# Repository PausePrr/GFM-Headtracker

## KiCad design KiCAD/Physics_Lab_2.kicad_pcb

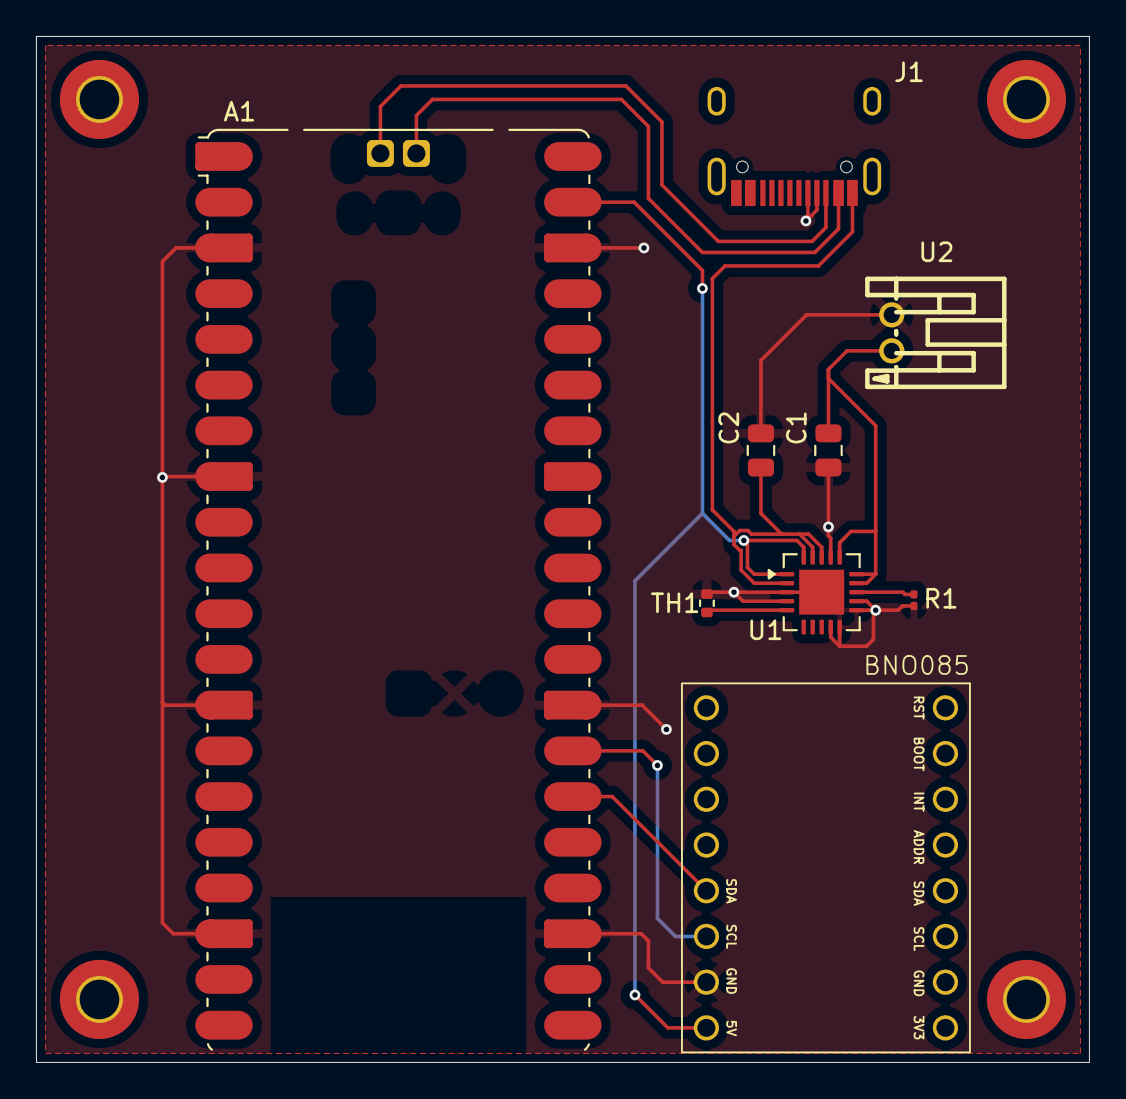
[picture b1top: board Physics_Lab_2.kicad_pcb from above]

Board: 2 copper layers, 58.5 x 57.0 mm, 9 parts (0 on the bottom side), 10 nets.

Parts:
A1: RaspberryPi_Pico_W; RaspberryPi_Pico_W_SMD
BNO085_Halley1: BNO085 Halley
C1: 4.7uF; C_0805_2012Metric
C2: 10uF; C_0805_2012Metric
J1: USB_C; HRO-TYPE-C-31-M-12
R1: 2K; R_0201_0603Metric
TH1: 10kΩ; R_0402_1005Metric
U1: MCP73871; QFN-20-1EP_4x4mm_P0.5mm_EP2.5x2.5mm
U2: S2B-PH-K-S-GW; CONN-TH_S2B-PH-K-S-GW

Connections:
GND: A1.3 (GND), A1.8 (GND), A1.13 (GND), A1.18 (GND), A1.23 (GND), A1.28 (GND), A1.38 (GND), BNO085_Halley1.15 (GND), C1.2, C2.1, J1.4 (GND), J1.5 (Shield), R1.1, TH1.1, U1.3 (SEL), U1.4 (PROG2), U1.9 (~TE), U1.10 (V_{SS}), U1.11 (V_{SS}), U1.12 (PROG3), U1.17 (CE), U1.21 (V_{SS}), U2.2
unnamed: A1.26 (GPIO20), BNO085_Halley1.13 (SDA)
unnamed: A1.27 (GPIO21), BNO085_Halley1.14 (SCL)
unnamed: A1.TP2 (USB_DM), J1.2 (D-)
unnamed: A1.TP3 (USB_DP), J1.3 (D+)
unnamed: A1.39 (VSYS), BNO085_Halley1.16 (5V), U1.1 (OUT), U1.20 (OUT)
unnamed: C2.2, J1.1 (VBUS), U1.2 (VPCC), U1.18 (IN), U1.19 (IN)
unnamed: R1.2, U1.13 (PROG1)
unnamed: TH1.2, U1.5 (THERM)
unnamed: C1.1, U1.14 (V_{BAT}), U1.15 (V_{BAT}), U1.16 (V_{BAT_SENSE}), U2.1

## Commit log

2026-02-10 ci: Add github workflows
2026-02-14 Add PCB and schematic files
2026-02-15 Rearrange PCB design
2026-02-16 Add mounting holes and remove errors
2026-02-22 Move KiCAD files to its respective directory
2026-02-22 Add PG and LBO connection to pico
2026-02-22 Remove TP1,4,5,6 and change TP2,3 to through hole
2026-02-24 Fix merge conflict by pause
